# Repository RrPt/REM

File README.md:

# REM
Rainers Energy Measurement

**Short englisch description:**  
*REM is an AC Energy Monitor based on the Analog Devices IC ADE7816 and a 
ESP32 microcontroller. It consists of one controlling module REM-C and one
to eight measuring modules REM-M, where each REM-M modul can measure up to 
12 different circuits. So totaly 96 circuits can be meassured.
Power data can be sent by MQTT or WebServer. The Webserver ist also used for configuration and calibration.*

*This project ist in german, to translate you can use a translator program like [here](https://translate.google.com/translate?hl=de&sl=auto&tl=en&u=https%3A%2F%2Fgithub.com%2FRrPt%2FREM)*

**Kurzbeschreibung:**  
REM ist ein Energiemonitor der auf dem Analog Device IC ADE7816 und einem Mikrocontroller ESP32 basiert.
Er besteht aus einem Kontrollermodul REM-C und einem bis acht Messmodulen REM-M. 
Jedes REM-M Modul kann 12 verschiedene Leistungskreise messen, so dass insgesamt bis zu 
96 Schaltkreise gemessen werden können.
Die Leistungsdaten können per MQTT versendet oder über einen Webserver abgefragt werden.
Der Webserver wird auch für die Konfiguration und die Kalibrierung verwendet.

Die Komponenten werden normalerweise in der Hausverteilung installiert und können dann die Leistung von z.B. einzelnen Zimmern erfassen.

Wine ausführliche Beschreibung ist im [Wiki](../../wiki/Home) zu finden.
## Übersicht
Das System besteht aus mehreren Hutschinenkomponenten, die über den REM-Bus miteinander verbunden sind

## [REM-C](../../wiki/REM-C) 
Das REM-C Modul enthält den Controller. Dieser fragt alle Messwerte über den 
REM-Bus von den einzelnen REM-M Modulen ab und stellt diesen über den 
Ethernetanschluß zur Verfügung. Die geschieht per MQTT und einen Webserver.
Über den Webserver erfolgt auch die Kalibrierung.

An das REM-C Modul werden auch die drei Phasen der Spannungssignale angeschlossen,
diese werden galvanisch getrennt und über den REM-Bus den einzelnen REM-M Modulen
 zur Verfügung gestellt.

Es können bis zu 8 REM-M Module mit je 12 Kanälen angeschlossen werden, 
insgesamt also bis zu 96 Kanäle.

Für die Platine des REM-C Moduls stehen die KICAD Pläne, 
die 3D-Modelle der Gehäuse (SCAD) und 
die Controllersoftware in C++ (Arduino) zur Verfügung. 

## [REM-M](../../wiki/REM-M) 
### [REM-MH](https://github.com/RrPt/REM/wiki/REM-MH) 
Das REM-M Modul beinhaltet zum einen ein Verteilermodul REM-MH, 
welches den REM-BUS auf die 2 REM-MM Module aufteilt.
Auf diesem wird auch per Jumper die Adresse des REM-M Moduls eingestellt.
### [REM-MM](../../wiki/REM-MM) 
Jedes REM-M Modul beinhaltet 2 REM-MM Platinen, die für die eigentliche 
Messung zuständig sind.
An jede REM-MM Platine können 6 Stromsensoren angeschlossen werden, 
zusammen mit der über den REM-Bus gelieferten Spannung 
(Phase über Jumper für alle 6 Sensoren gleich einstellbar)
können so für alle 6 Kanäle die folgenden Energieparameter bestimmt werden:
 * Strom RMS
 * Leistung
 * Blindleistung
 
Pro REM-MM Platine:
 * Spannung RMS
 * Frequenz

Für die Platinen des REM-M Moduls stehen die KICAD Pläne und 
die 3D-Modelle der Gehäuse (SCAD) zur Verfügung. 

## Status
Das Projekt ist fertiggestellt und bei mir seit Anfang 2021 ununterbrochen ohne Probleme im Betrieb.

## Bilder

## Stichwörter
 * ADE7816, Energy Metering IC
 * ESP32
 * TCA9548A
 * USR ES1
 * Leistungsmessung, Blindleistungsmessung, Spannungsmessung, Strommessung, RMS
 * Stromwandler, Current transformer, ZMPT107-1, CT1005
 * Energiemonitor

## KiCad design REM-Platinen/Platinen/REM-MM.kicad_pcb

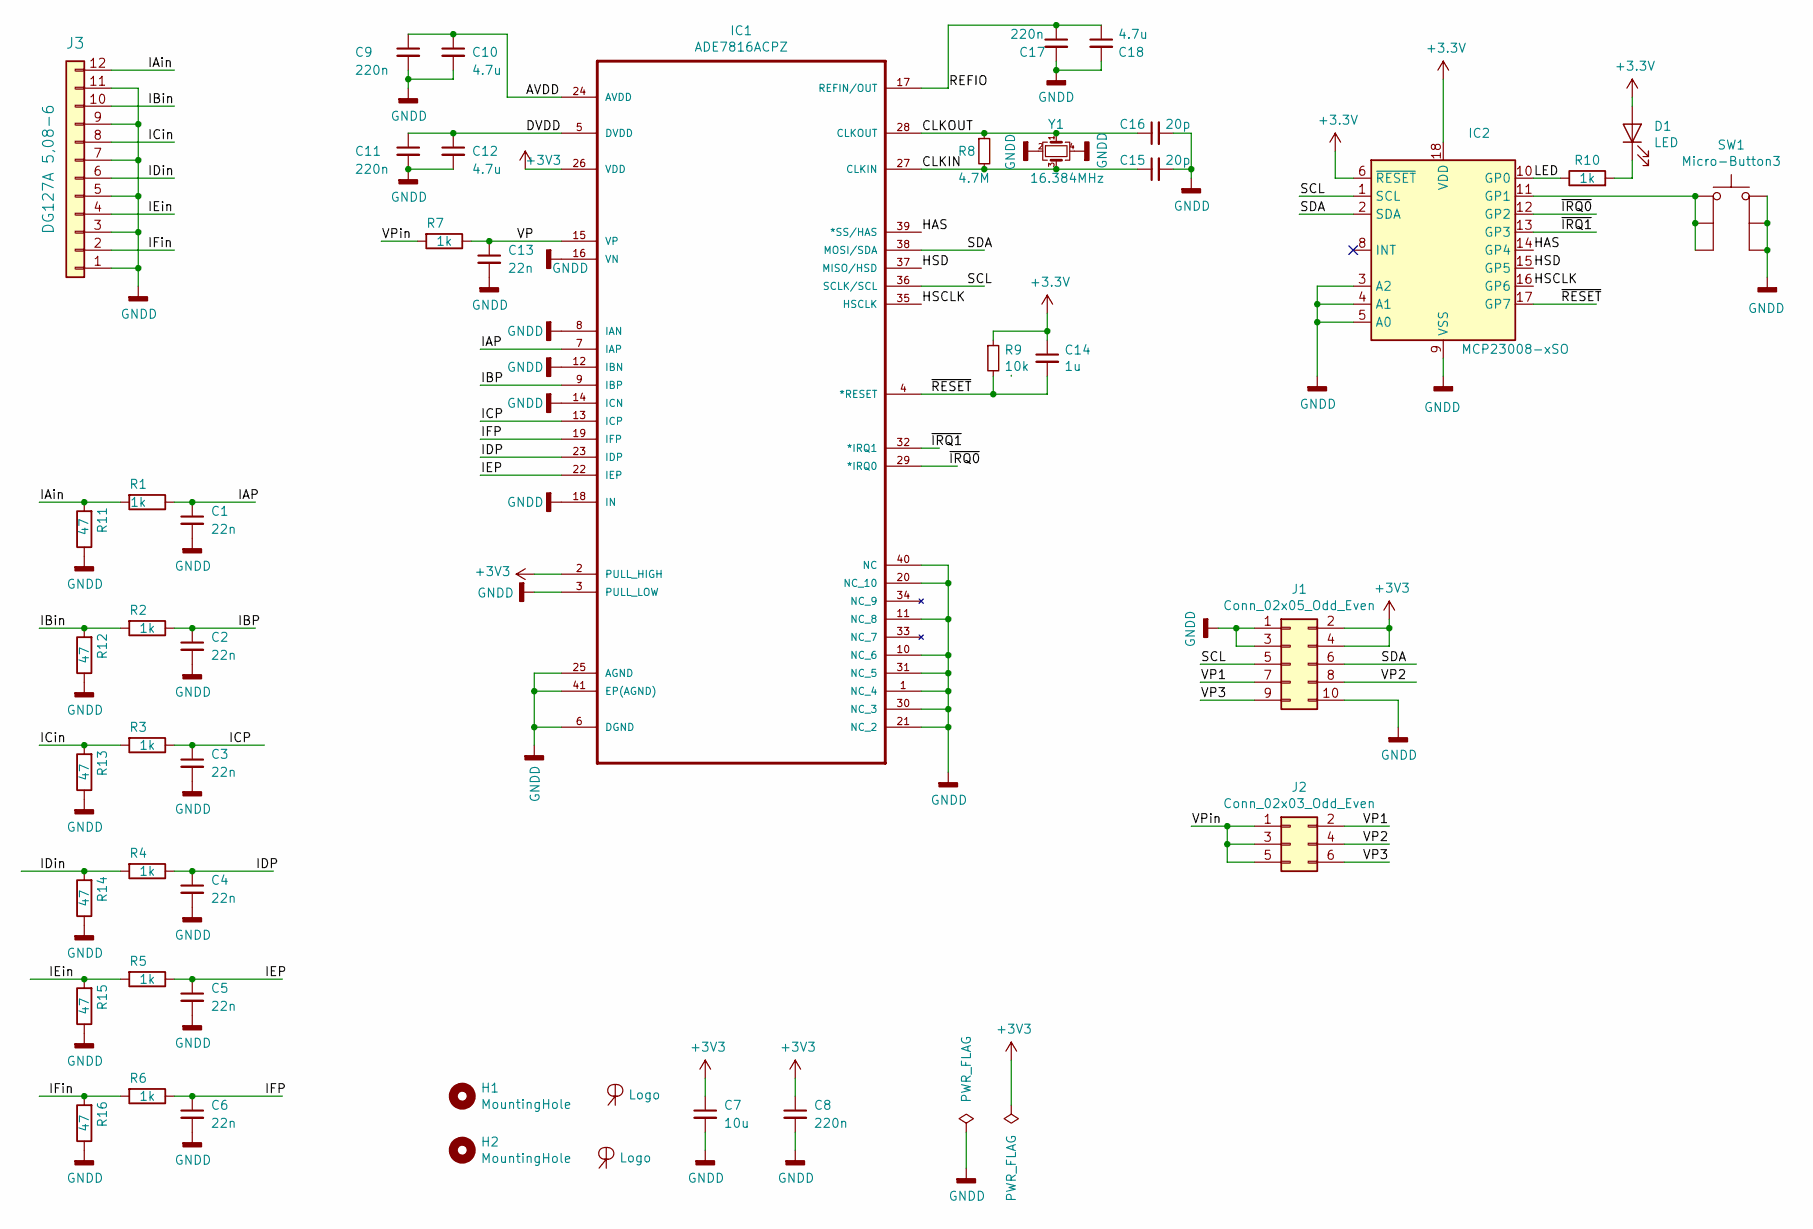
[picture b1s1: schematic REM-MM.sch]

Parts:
C1, C2, C3, C4, C5, C6, C13: 22n; C_0603_1608Metric
C7: 10u; C_1206_3216Metric
C8, C9, C11, C17: 220n; C_0603_1608Metric
C10, C12, C18: 4.7u; C_1206_3216Metric
C14: 1u; C_0603_1608Metric
C15, C16: 20p; C_0603_1608Metric
D1: LED; LED_D3.0mm_long
H1, H2: MountingHole; MountingHole_2.2mm_M2
IC1: ADE7816ACPZ; QFN50P600X600X80-41N
IC2: MCP23008-xSO; SOIC-18W_7.5x11.6mm_P1.27mm
J1: Conn_02x05_Odd_Even; PinHeader_2x05_P2.54mm_Vertical_mit_Stecker
J2: Conn_02x03_Odd_Even; PinHeader_2x03_P2.54mm_Vertical
J3: DG127A 5,08-6; pxc_1726189_05_MKKDSN-1-5-6-5-08
L1, L2: Logo; LogoRP_6mm
R1, R2, R3, R4, R5, R6, R7, R10: 1k; R_0603_1608Metric
R8: 4.7M; R_0603_1608Metric
R9: 10k; R_0603_1608Metric
R11, R12, R13, R14, R15, R16: 47; R_0603_1608Metric
SW1: Micro-Button3
Y1: 16.384MHz; Crystal_SMD_2520-4Pin_2.5x2.0mm

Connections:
/AVDD: C9.1, C10.1, IC1.24 (AVDD)
/CLKIN: C15.1, IC1.27 (CLKIN), R8.2, Y1.3
/CLKOUT: C16.1, IC1.28 (CLKOUT), R8.1, Y1.1
/DVDD: C11.1, C12.1, IC1.5 (DVDD)
/HAS: IC1.39 (*SS/HAS), IC2.14 (GP4)
/HSCLK: IC1.35 (HSCLK), IC2.16 (GP6)
/HSD: IC1.37 (MISO/HSD), IC2.15 (GP5)
/IAP: C1.1, IC1.7 (IAP), R1.1
/IAin: J3.12, R1.2, R11.2
/IBP: C2.1, IC1.9 (IBP), R2.1
/IBin: J3.10, R2.2, R12.2
/ICP: C3.1, IC1.13 (ICP), R3.1
/ICin: J3.8, R3.2, R13.2
/IDP: C4.1, IC1.23 (IDP), R4.1
/IDin: J3.6, R4.2, R14.2
/IEP: C5.1, IC1.22 (IEP), R5.1
/IEin: J3.4, R5.2, R15.2
/IFP: C6.1, IC1.19 (IFP), R6.1
/IFin: J3.2, R6.2, R16.2
/LED: IC2.10 (GP0), R10.1
/REFIO: C17.1, C18.1, IC1.17 (REFIN/OUT)
/SCL: IC1.36 (SCLK/SCL), IC2.1 (SCL), J1.5
/SDA: IC1.38 (MOSI/SDA), IC2.2 (SDA), J1.6
/VP: C13.1, IC1.15 (VP), R7.1
/VP1: J1.7, J2.2
/VP2: J1.8, J2.4
/VP3: J1.9, J2.6
/VPin: J2.1, J2.3, J2.5, R7.2
/~IRQ0: IC1.29 (*IRQ0), IC2.12 (GP2)
/~IRQ1: IC1.32 (*IRQ1), IC2.13 (GP3)
/~RESET: C14.2, IC1.4 (*RESET), IC2.17 (GP7), R9.2
GNDD: C1.2, C2.2, C3.2, C4.2, C5.2, C6.2, C7.2, C8.2, C9.2, C10.2, C11.2, C12.2, C13.2, C15.2, C16.2, C17.2, C18.2, IC1.1 (NC_4), IC1.3 (PULL_LOW), IC1.6 (DGND), IC1.8 (IAN), IC1.10 (NC_6), IC1.11 (NC_8), IC1.12 (IBN), IC1.14 (ICN), IC1.16 (VN), IC1.18 (IN), IC1.20 (NC_10), IC1.21 (NC_2), IC1.25 (AGND), IC1.30 (NC_3), IC1.31 (NC_5), IC1.40 (NC), IC1.41 (EP(AGND)), IC2.3 (A2), IC2.4 (A1), IC2.5 (A0), IC2.9 (VSS), J1.1, J1.3, J1.10, J3.1, J3.3, J3.5, J3.7, J3.9, J3.11, R11.1, R12.1, R13.1, R14.1, R15.1, R16.1, SW1.2, SW1.4, SW1.6, Y1.2, Y1.4
unnamed: D1.1 (K), R10.2
unnamed: IC2.11 (GP1), SW1.1, SW1.3, SW1.5

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
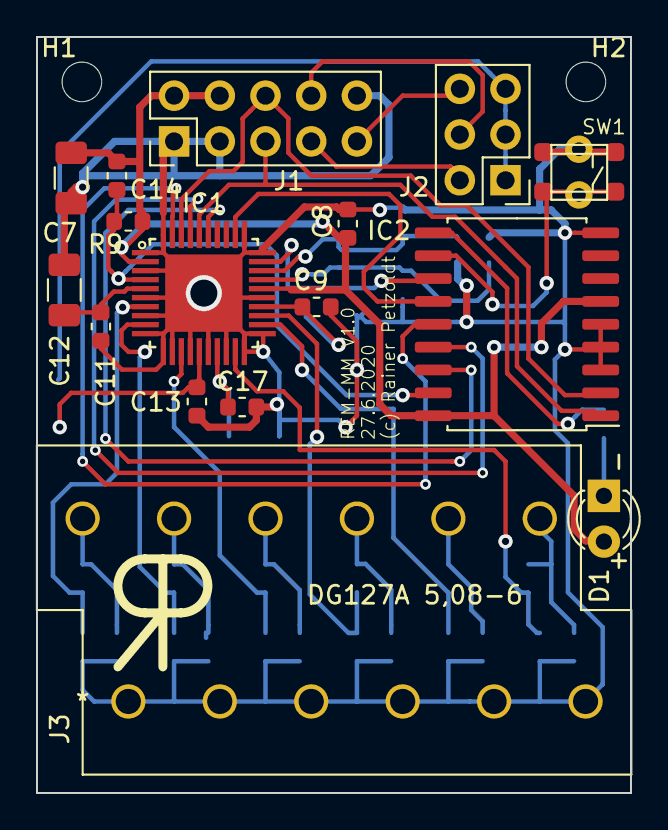
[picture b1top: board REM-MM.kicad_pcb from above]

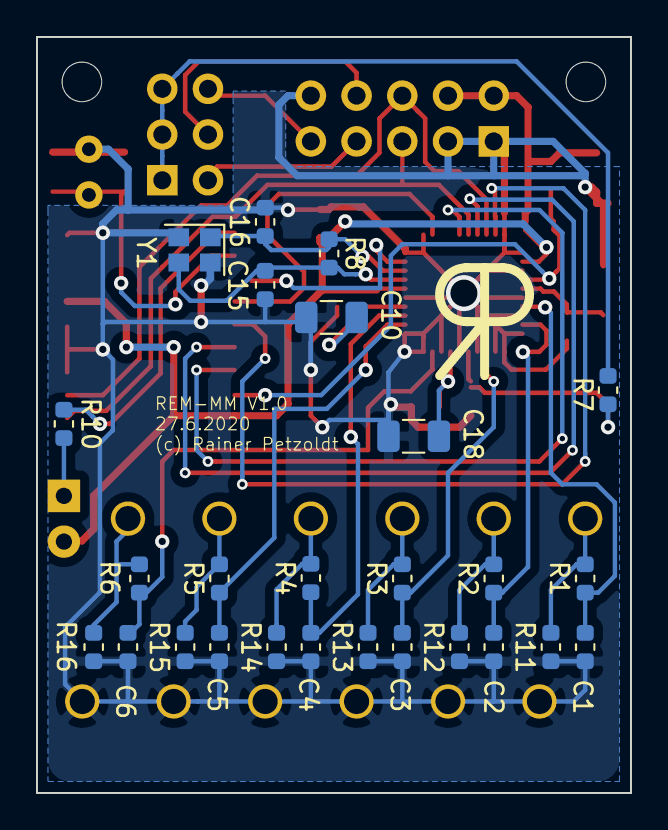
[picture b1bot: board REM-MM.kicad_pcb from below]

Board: 2 copper layers, 33.0 x 42.0 mm, 46 parts (27 on the bottom side), 35 nets.

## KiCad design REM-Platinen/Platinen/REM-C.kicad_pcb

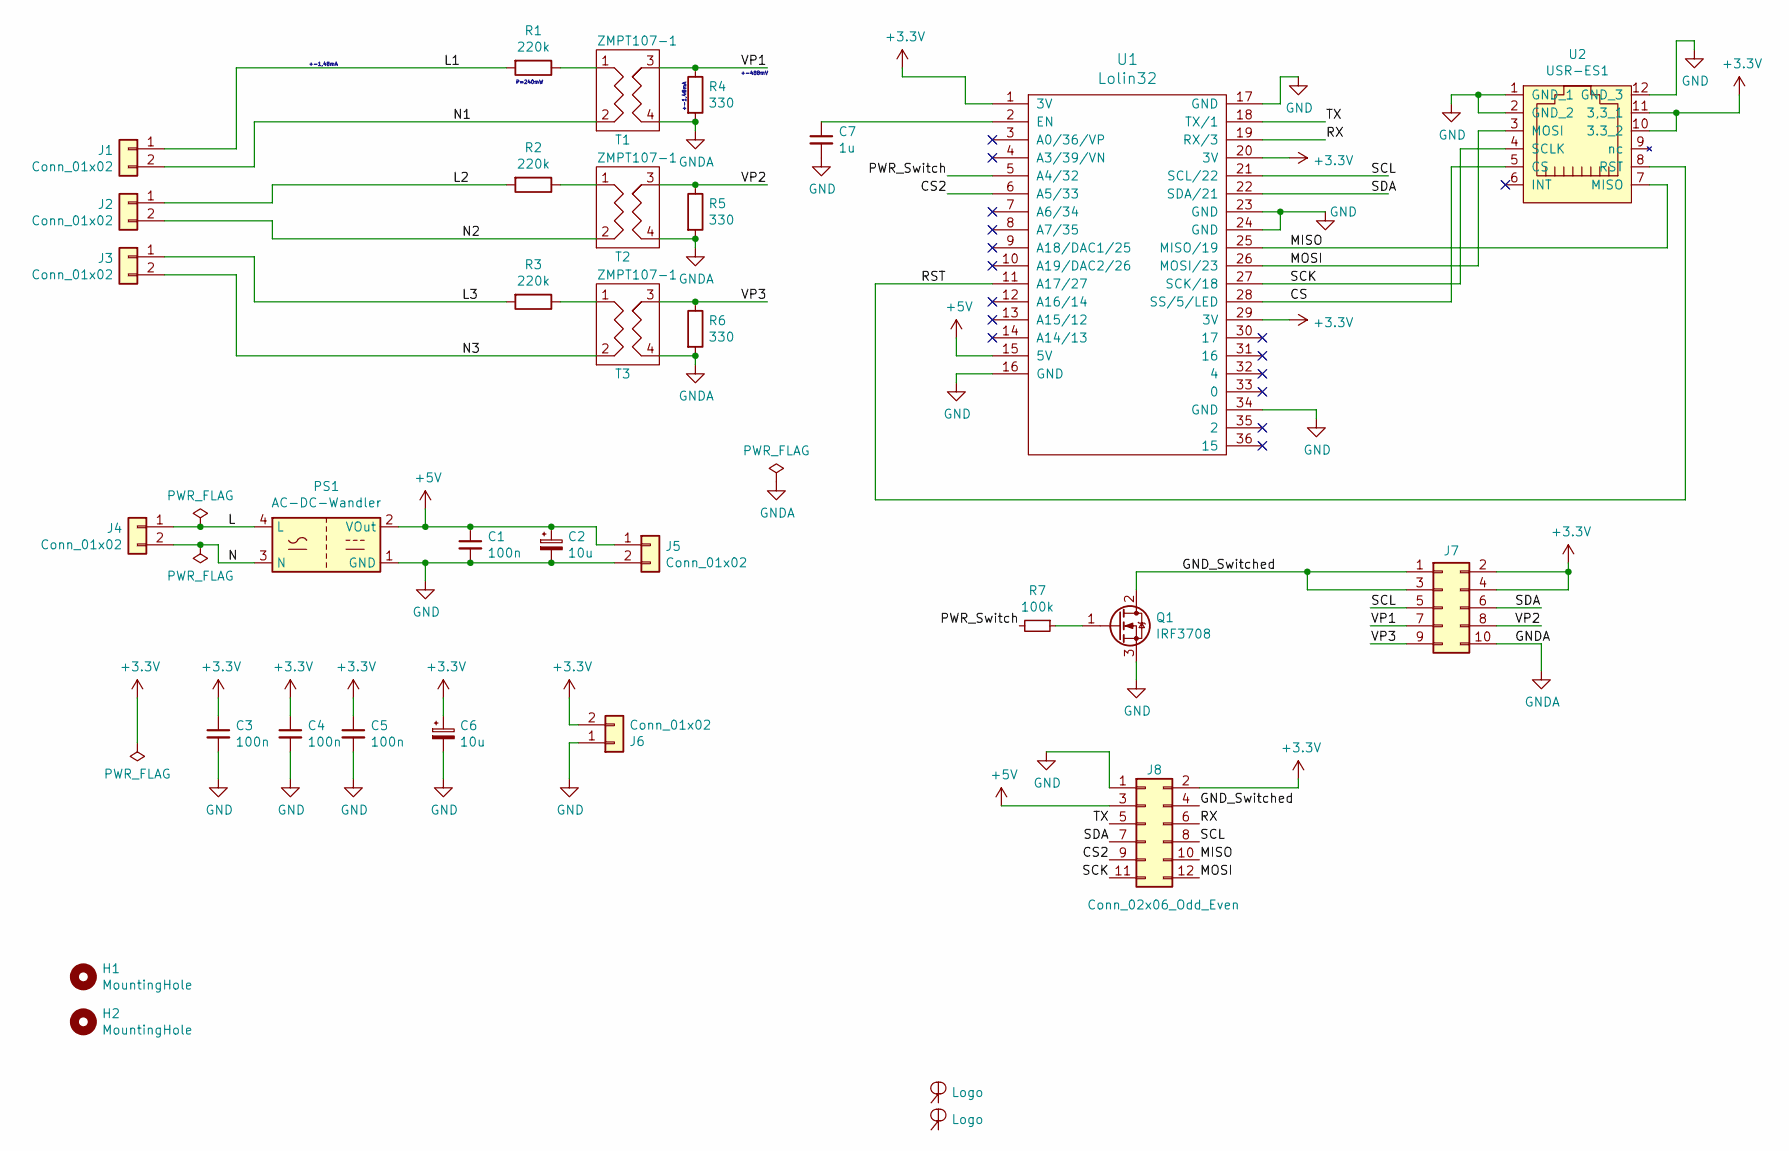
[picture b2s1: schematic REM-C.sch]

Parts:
C1, C3, C4, C5: 100n; C_0603_1608Metric
C2, C6: 10u; CP_Radial_D5.0mm_P2.00mm
C7: 1u; C_0805_2012Metric
H1, H2: MountingHole; MountingHole_2.2mm_M2
J1, J2, J3, J4, J5, J6: Conn_01x02; W237-102
J7: Conn_02x05_Odd_Even; PinHeader_2x05_P2.54mm_Vertical_mit_Stecker
J8: Conn_02x06_Odd_Even; PinHeader_2x06_P2.54mm_Vertical
L1, L2: Logo; LogoRP_6mm
PS1: AC-DC-Wandler; AC-DC_Wandler
Q1: IRF3708; TO-220-3_Vertical
R1, R2, R3: 220k; R_Axial_DIN0414_L11.9mm_D4.5mm_P15.24mm_Horizontal
R4, R5, R6: 330; R_Axial_DIN0207_L6.3mm_D2.5mm_P10.16mm_Horizontal
R7: 100k; R_0603_1608Metric
T1, T2, T3: ZMPT107-1; ZMPT107
U1: Lolin32; Lolin32_gesockelt
U2: USR-ES1; USR-ES1_gesockelt

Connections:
+3V3: C3.1, C4.1, C5.1, C6.1, J6.2, J7.2, J7.4, J8.2, U1.1 (3V), U1.20 (3V), U1.29 (3V), U2.10 (3.3_2), U2.11 (3,3_1)
+5V: C1.1, C2.1, J5.1, J8.3, PS1.2 (VOut), U1.15 (5V)
/CS: U1.28 (SS/5/LED), U2.5 (CS)
/CS2: J8.9, U1.6 (A5/33)
/GND_Switched: J7.1, J7.3, J8.4, Q1.2 (D)
/L: J4.1, PS1.4 (L)
/L1: J1.1, R1.2
/L2: J2.1, R2.2
/L3: J3.1, R3.2
/MISO: J8.10, U1.25 (MISO/19), U2.7 (MISO)
/MOSI: J8.12, U1.26 (MOSI/23), U2.3 (MOSI)
/N: J4.2, PS1.3 (N)
/N1: J1.2, T1.2
/N2: J2.2, T2.2
/N3: J3.2, T3.2
/PWR_Switch: R7.2, U1.5 (A4/32)
/RST: U1.11 (A17/27), U2.8 (RST)
/RX: J8.6, U1.19 (RX/3)
/SCK: J8.11, U1.27 (SCK/18), U2.4 (SCLK)
/SCL: J7.5, J8.8, U1.21 (SCL/22)
/SDA: J7.6, J8.7, U1.22 (SDA/21)
/TX: J8.5, U1.18 (TX/1)
/VP1: J7.7, R4.1, T1.3
/VP2: J7.8, R5.1, T2.3
/VP3: J7.9, R6.1, T3.3
GND: C1.2, C2.2, C3.2, C4.2, C5.2, C6.2, C7.2, J5.2, J6.1, J8.1, PS1.1 (GND), Q1.3 (S), U1.16 (GND), U1.17 (GND), U1.23 (GND), U1.24 (GND), U1.34 (GND), U2.1 (GND_1), U2.2 (GND_2~), U2.12 (GND_3)
GNDA: J7.10, R4.2, R5.2, R6.2, T1.4, T2.4, T3.4
unnamed: C7.1, U1.2 (EN)
unnamed: Q1.1 (G), R7.1
unnamed: R1.1, T1.1
unnamed: R2.1, T2.1
unnamed: R3.1, T3.1

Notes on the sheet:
+-1,48mA
P=240mW
+-488mV

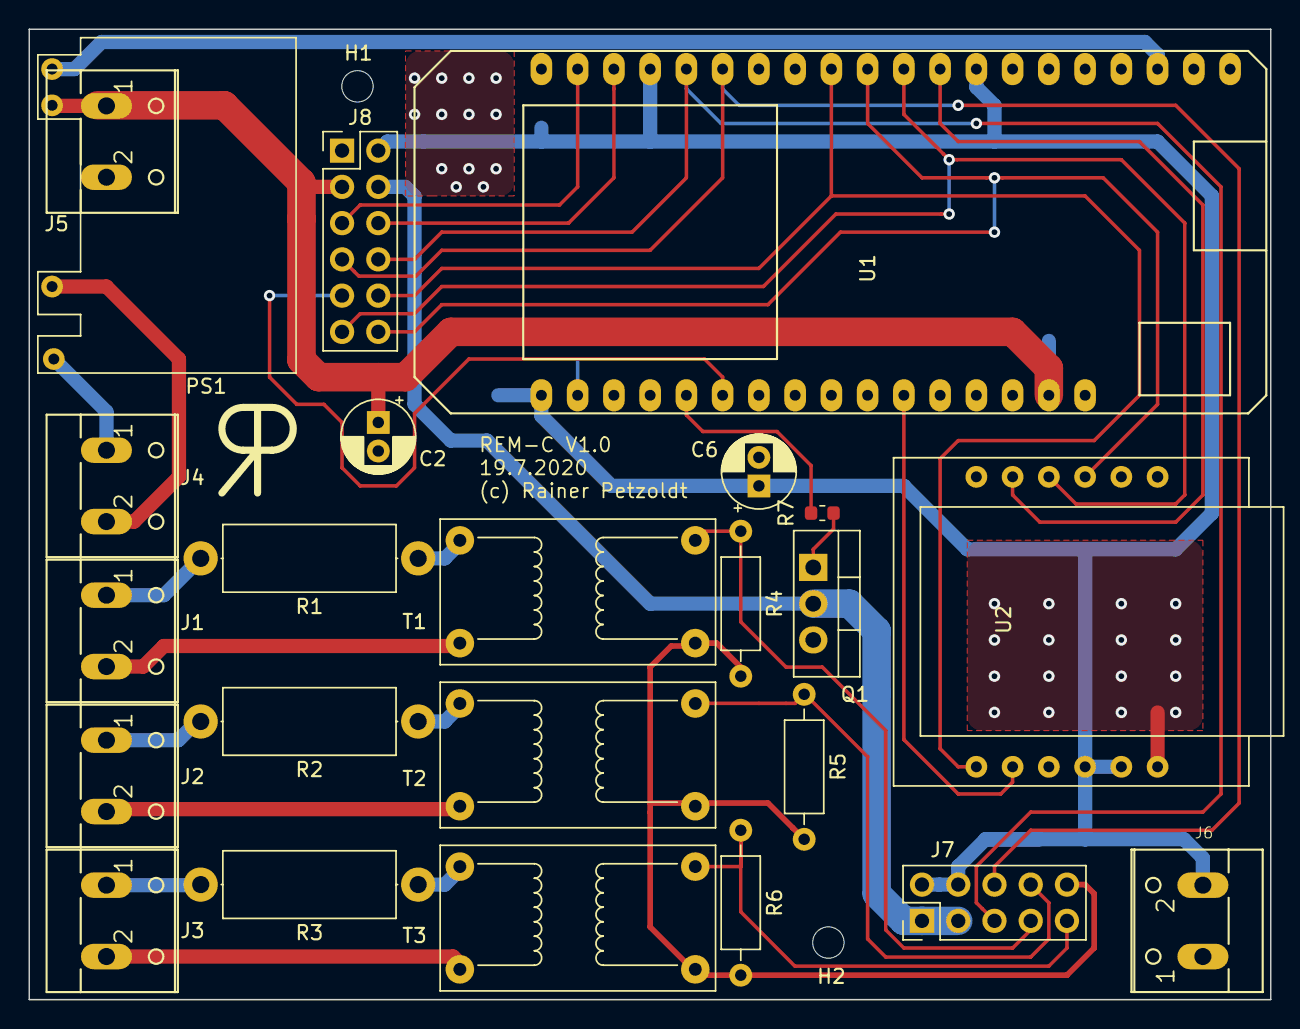
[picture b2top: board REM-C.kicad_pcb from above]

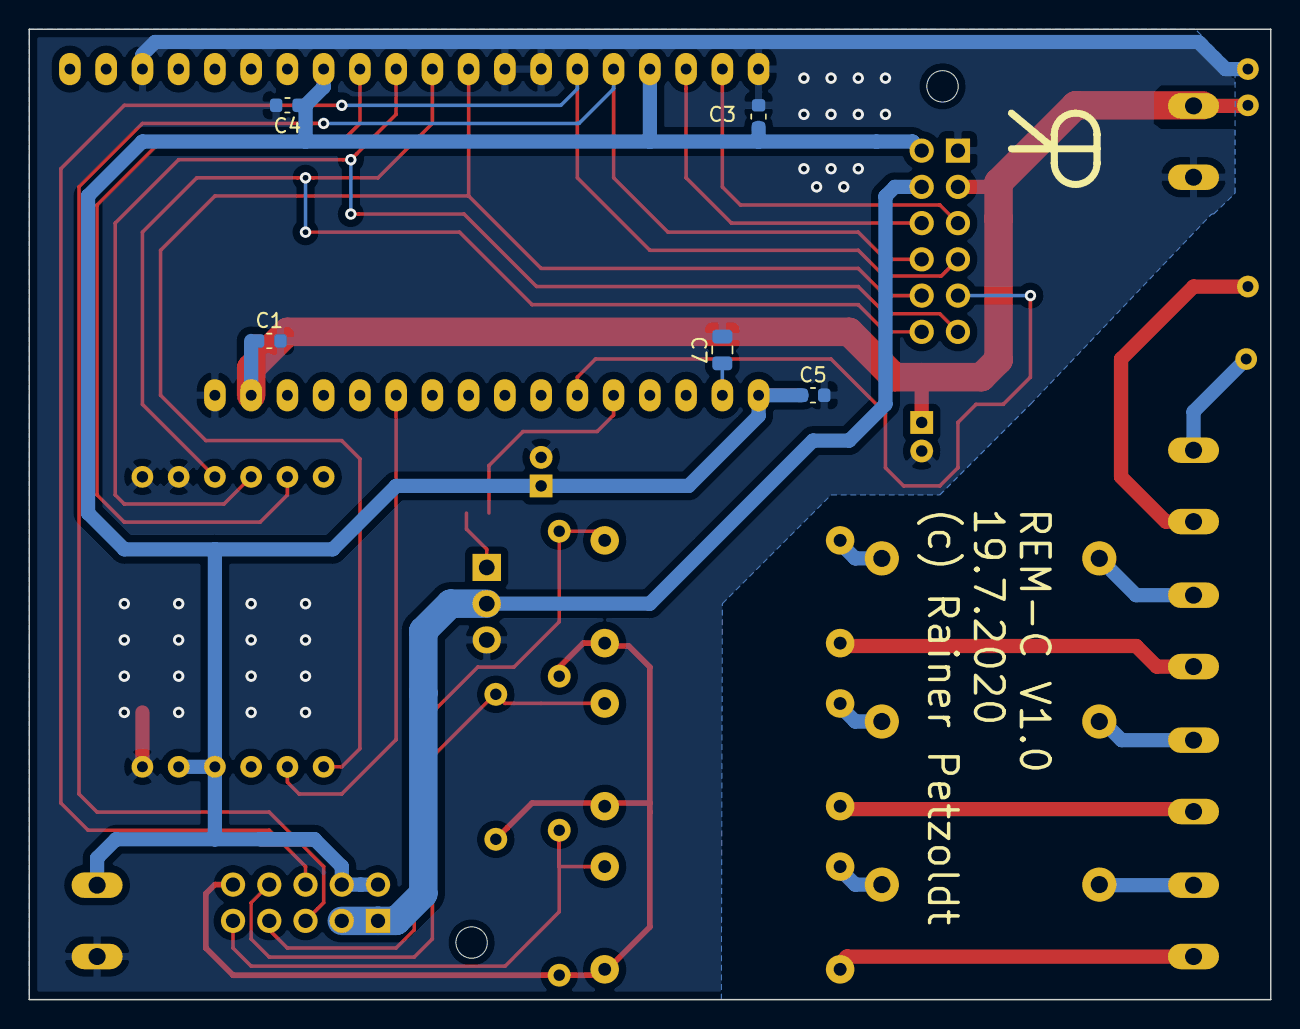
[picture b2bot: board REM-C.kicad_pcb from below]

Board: 2 copper layers, 87.0 x 68.0 mm, 33 parts (6 on the bottom side), 32 nets.

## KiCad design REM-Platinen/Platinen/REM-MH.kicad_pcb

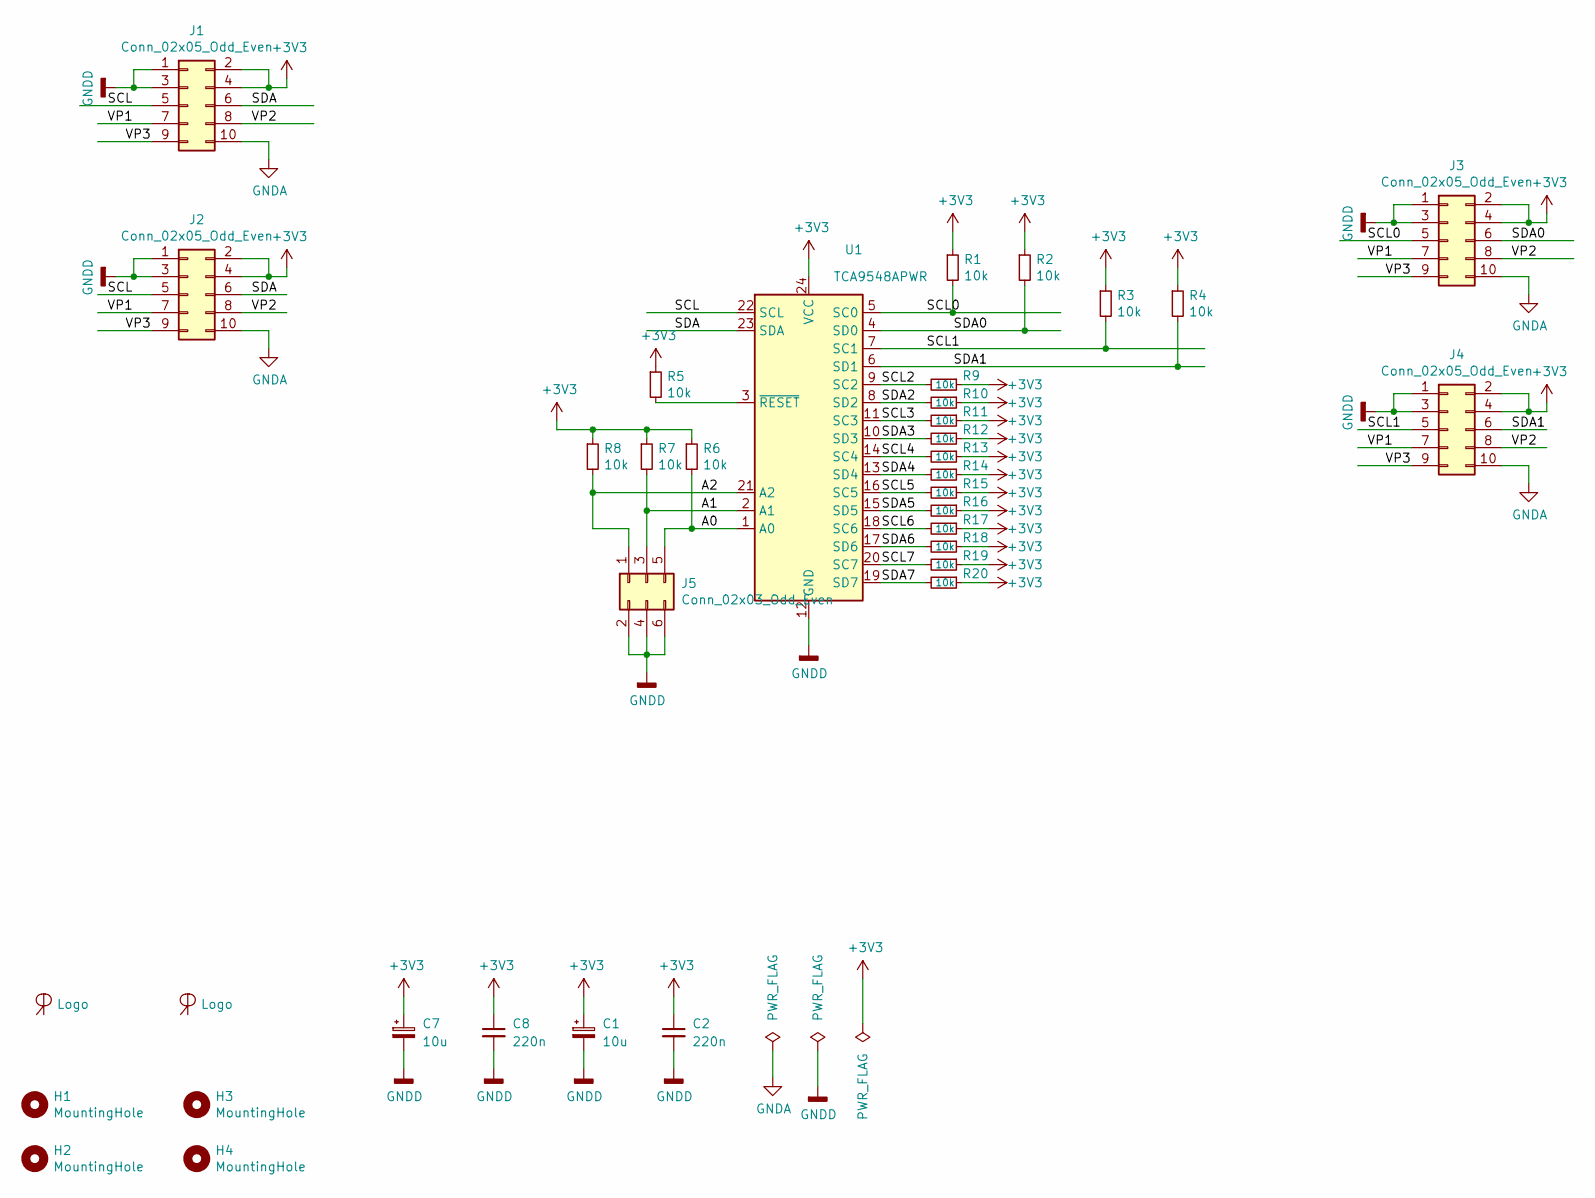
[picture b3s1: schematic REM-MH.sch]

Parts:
C1, C7: 10u; C_1206_3216Metric
C2, C8: 220n; C_0603_1608Metric
H1, H2, H3, H4: MountingHole; MountingHole_2.2mm_M2
J1, J2, J3, J4: Conn_02x05_Odd_Even; PinHeader_2x05_P2.54mm_Vertical_mit_Stecker
J5: Conn_02x03_Odd_Even; PinHeader_2x03_P2.54mm_Vertical
L1, L2: Logo; LogoRP_6mm
R1, R2, R3, R4, R5, R6, R7, R8, R9, R10, R11, R12, R13, R14, R15, R16, R17, R18, R19, R20: 10k; R_0603_1608Metric
U1: TCA9548APWR; TSSOP-24_4.4x7.8mm_P0.65mm

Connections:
+3V3: C1.1, C2.1, C7.1, C8.1, J1.2, J1.4, J2.2, J2.4, J3.2, J3.4, J4.2, J4.4, R1.1, R2.1, R3.1, R4.1, R5.1, R6.1, R7.1, R8.1, R9.1, R10.1, R11.1, R12.1, R13.1, R14.1, R15.1, R16.1, R17.1, R18.1, R19.1, R20.1, U1.24 (VCC)
/A0: J5.5, R6.2, U1.1 (A0)
/A1: J5.3, R7.2, U1.2 (A1)
/A2: J5.1, R8.2, U1.21 (A2)
/SCL: J1.5, J2.5, U1.22 (SCL)
/SCL0: J3.5, R1.2, U1.5 (SC0)
/SCL1: J4.5, R3.2, U1.7 (SC1)
/SCL2: R9.2, U1.9 (SC2)
/SCL3: R11.2, U1.11 (SC3)
/SCL4: R13.2, U1.14 (SC4)
/SCL5: R15.2, U1.16 (SC5)
/SCL6: R17.2, U1.18 (SC6)
/SCL7: R19.2, U1.20 (SC7)
/SDA: J1.6, J2.6, U1.23 (SDA)
/SDA0: J3.6, R2.2, U1.4 (SD0)
/SDA1: J4.6, R4.2, U1.6 (SD1)
/SDA2: R10.2, U1.8 (SD2)
/SDA3: R12.2, U1.10 (SD3)
/SDA4: R14.2, U1.13 (SD4)
/SDA5: R16.2, U1.15 (SD5)
/SDA6: R18.2, U1.17 (SD6)
/SDA7: R20.2, U1.19 (SD7)
/VP1: J1.7, J2.7, J3.7, J4.7
/VP2: J1.8, J2.8, J3.8, J4.8
/VP3: J1.9, J2.9, J3.9, J4.9
GNDA: J1.10, J2.10, J3.10, J4.10
GNDD: C1.2, C2.2, C7.2, C8.2, J1.1, J1.3, J2.1, J2.3, J3.1, J3.3, J4.1, J4.3, J5.2, J5.4, J5.6, U1.12 (GND)
unnamed: R5.2, U1.3 (~RESET)

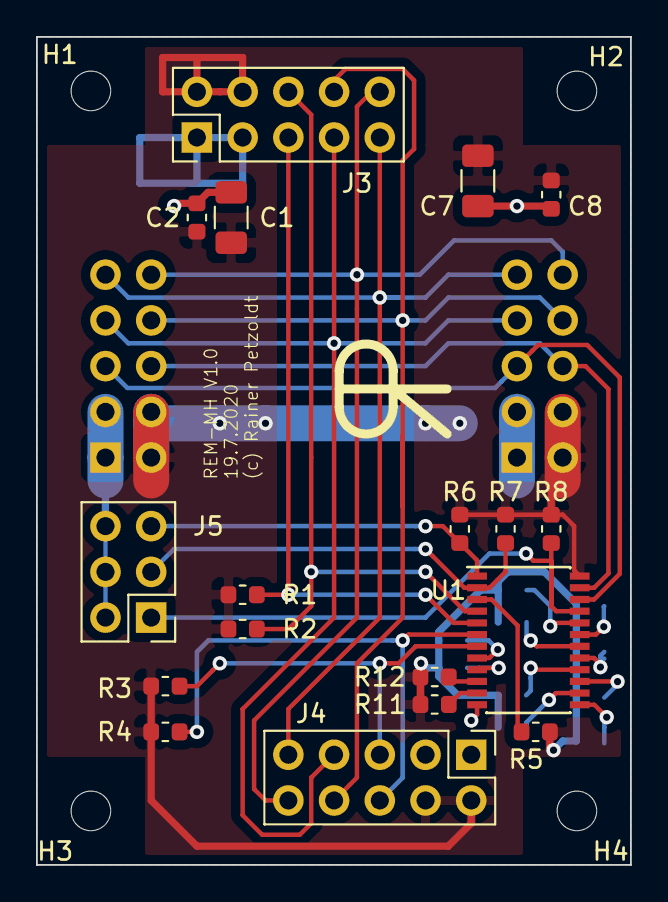
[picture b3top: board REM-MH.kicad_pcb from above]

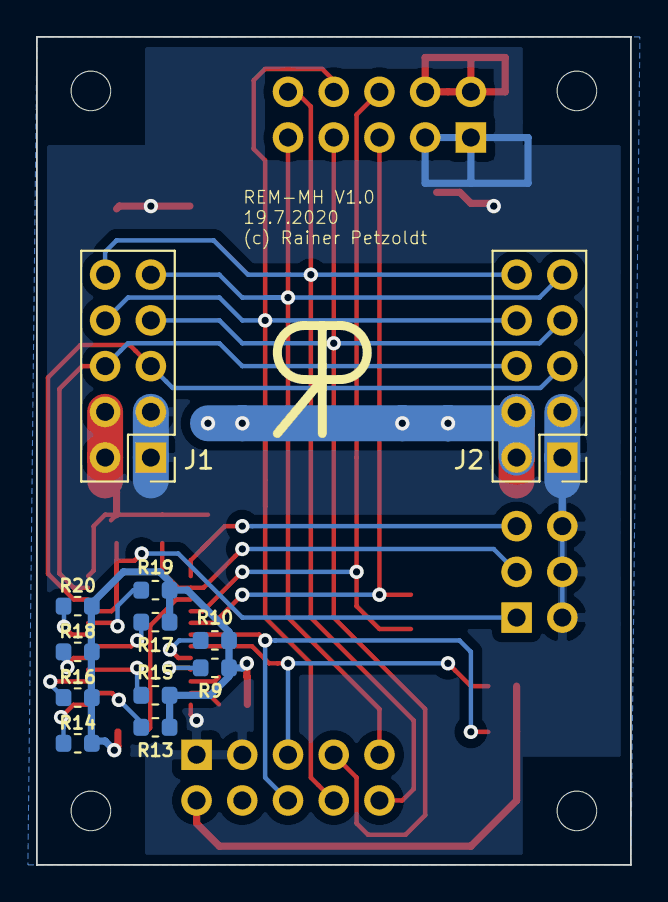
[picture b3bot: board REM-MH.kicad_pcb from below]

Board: 2 copper layers, 33.0 x 46.0 mm, 36 parts (13 on the bottom side), 28 nets.

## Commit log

2020-09-13 test3
2020-09-15 Erste Beschreibung
2020-09-15 Übersicht ergänzt
2020-09-15 Beschreibungsseite überarbeitet
2020-09-21 Bilder in Unterordner verschoben
2020-09-21 Update README.md
    Bildpfade berichtigt
2020-09-23 Tippfehler behoben
2020-09-23 Verweis auf Wiki
2020-09-23 Platinen veröffentlicht
2020-09-23 Pfade ins wiki relativ
2020-09-23 3d Daten der Gehäuse veröffentlicht
2021-04-05 First published Version of REM project
2023-05-31 Update README.md
    Status aktualisiert
2023-05-31 Update README.md
    Tippfehler

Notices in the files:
parts and their libraries:
Copyright 2016 Accelerated Designs. All rights reserved.
